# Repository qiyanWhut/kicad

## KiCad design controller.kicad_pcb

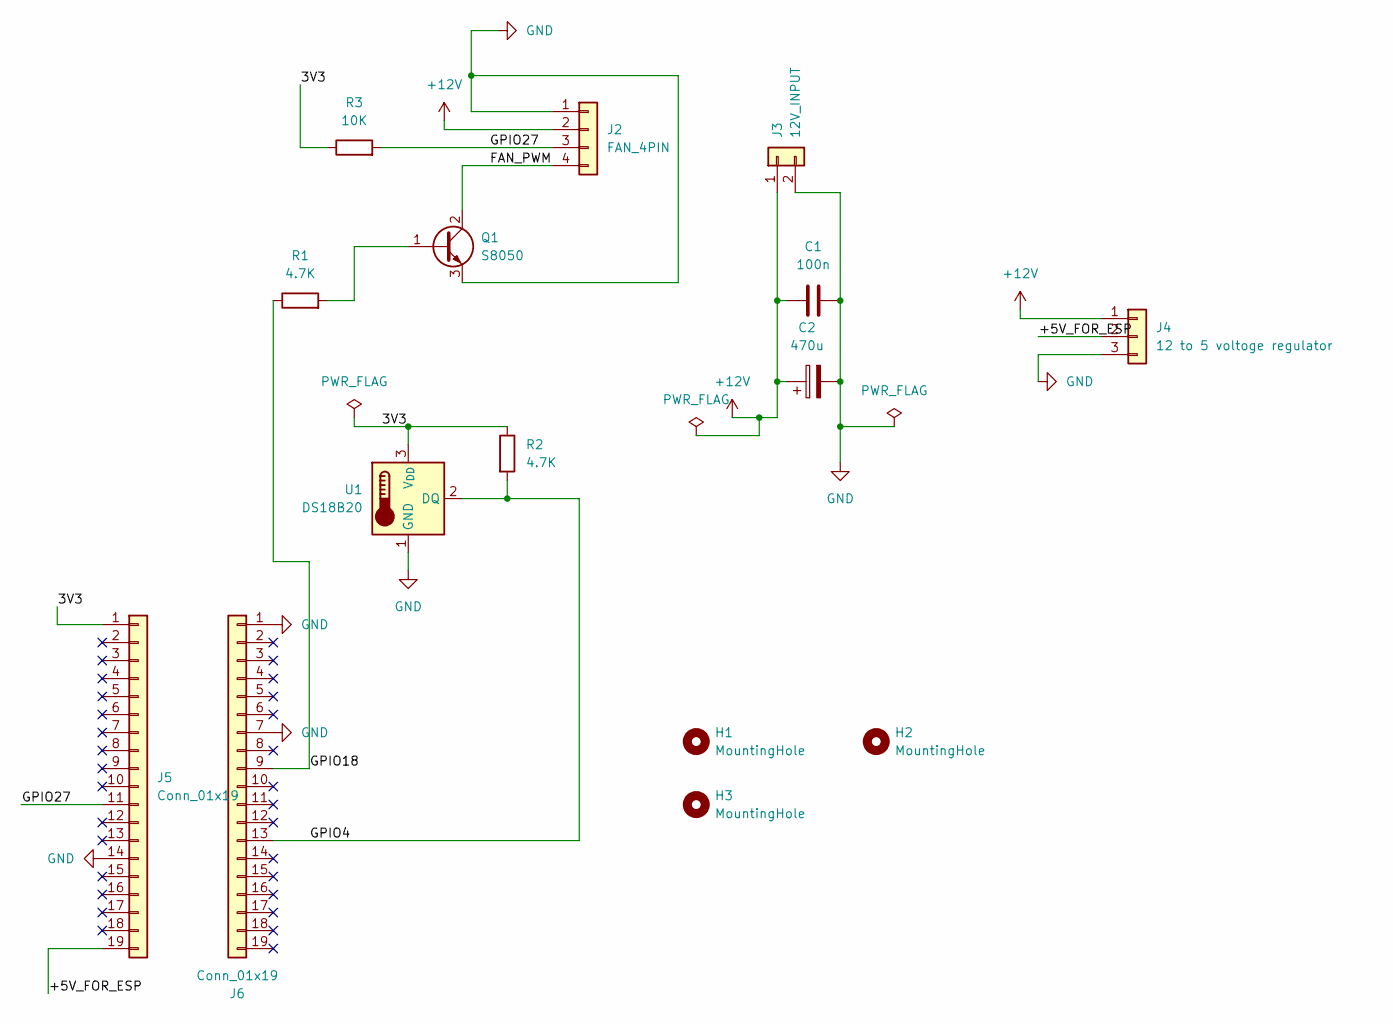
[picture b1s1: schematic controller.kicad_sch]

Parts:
C1: 100n; C_Disc_D5.0mm_W2.5mm_P5.00mm
C2: 470u; C_Radial_D10.0mm_H16.0mm_P5.00mm
H1, H2, H3: MountingHole; MountingHole_3.2mm_M3
J2: FAN_4PIN; PinHeader_1x04_P2.54mm_Vertical
J3: 12V_INPUT; TerminalBlock_Phoenix_MKDS-1,5-2-5.08_1x02_P5.08mm_Horizont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
J4: 12 to 5 voltoge regulator; PinHeader_1x03_P2.54mm_Horizontal
J5, J6: Conn_01x19; PinSocket_1x19_P2.54mm_Vertical
Q1: S8050; TO-92_Inline
R1, R2: 4.7K; R_Axial_DIN0207_L6.3mm_D2.5mm_P10.16mm_Horizontal
R3: 10K; R_Axial_DIN0207_L6.3mm_D2.5mm_P10.16mm_Horizontal
U1: DS18B20; TO-92_Inline

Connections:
+12V: C1.1, C2.1, J2.2, J3.1, J4.1
/3V3: J5.1, R2.1, R3.1, U1.3 (V_{DD})
/+5V_FOR_ESP: J4.2, J5.19
/FAN_PWM: J2.4, Q1.2 (C)
/GPIO4: J6.13, R2.2, U1.2 (DQ)
/GPIO18: J6.9, R1.1
/GPIO27: J2.3, J5.11, R3.2
GND: C1.2, C2.2, J2.1, J3.2, J4.3, J5.14, J6.1, J6.7, Q1.3 (E), U1.1 (GND)
unnamed: Q1.1 (B), R1.2

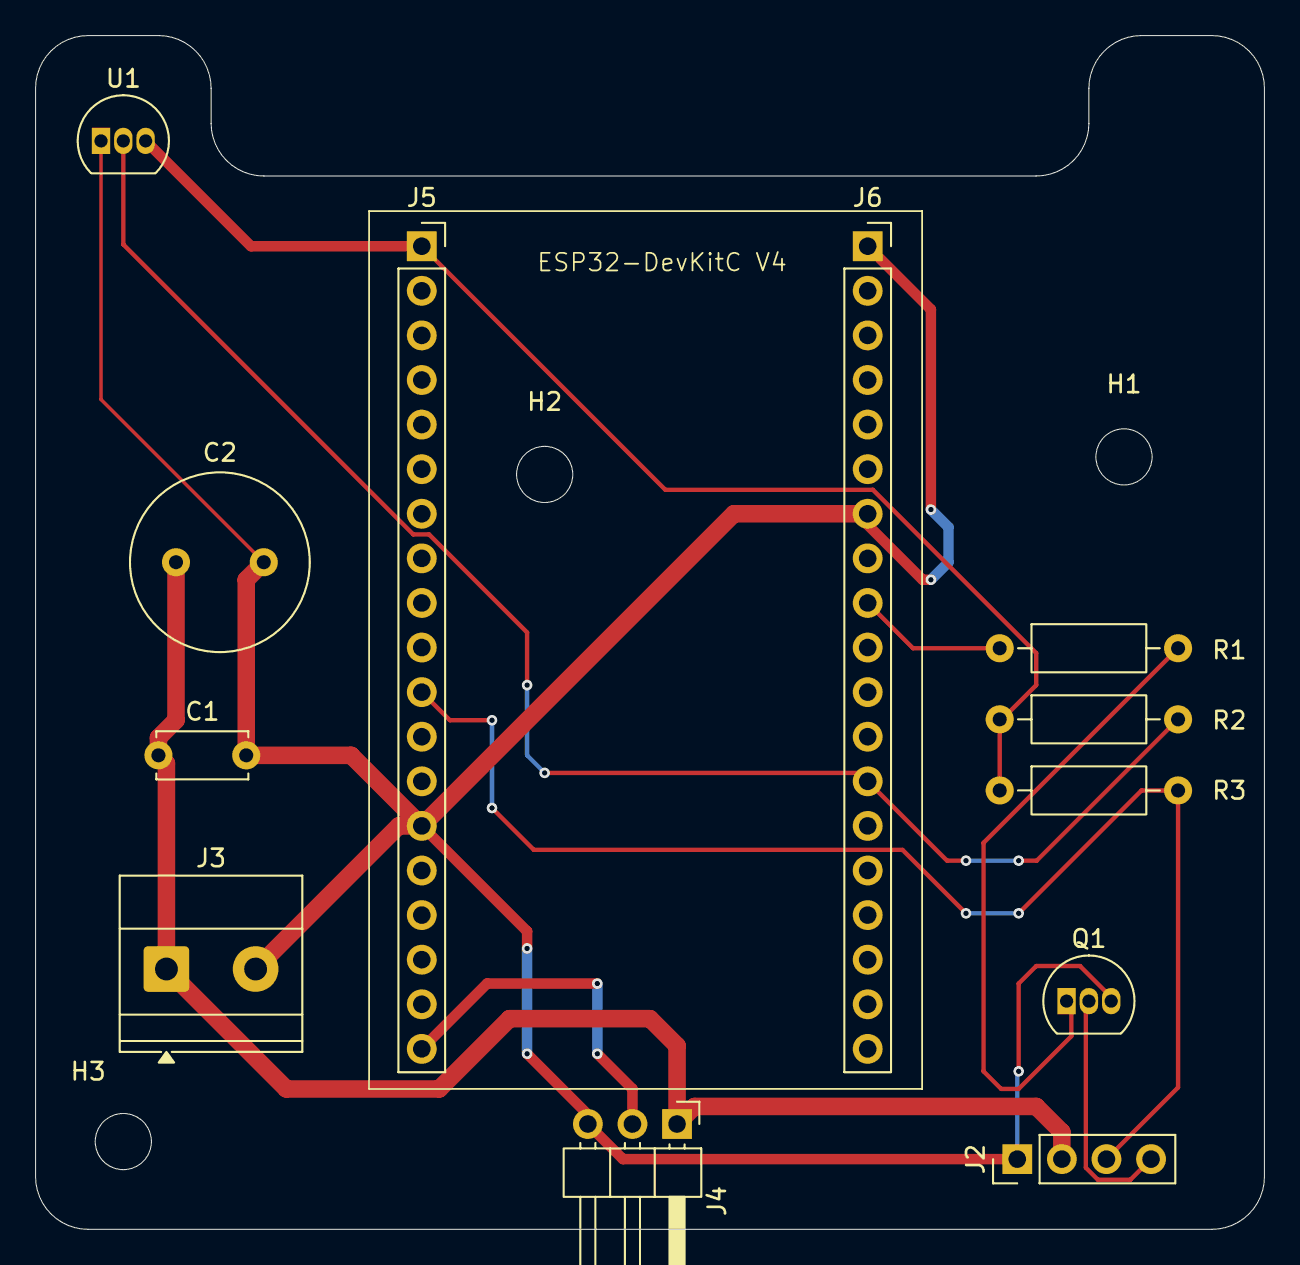
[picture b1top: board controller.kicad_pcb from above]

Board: 2 copper layers, 70.0 x 68.0 mm, 15 parts (0 on the bottom side), 9 nets.
